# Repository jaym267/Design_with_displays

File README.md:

# Design with Displays – Week 4: RGB Mood Light

For week 4 of Hack Club Half-Life, I designed a small RGB mood light board. A Seeed XIAO RP2040 drives a 5 mm RGB LED. A push button cycles through 7 colours, and a slide potentiometer sets the brightness from off to full.

## What I did
 
### 1. Planned the project
I followed the Tier 1 "5 mm LEDs" guide and picked the RGB mood light as my build: one common-cathode RGB LED, a slide pot, and a button, all controlled by a XIAO RP2040.

### 2. Drew the schematic in KiCad
- I created a new KiCad project and placed the XIAO RP2040, an RGB LED (LED_RKGB), three resistors, a 10 kΩ slide pot, a push button, and the power symbols.
- I picked the resistor values from the LED's forward voltage: 270 Ω for red (about 2.0 V) and 100 Ω for green and blue (about 3.0 V), all running from a 3.3 V pin.
- I wired each colour through its resistor to the LED, the LED's common cathode to GND, the pot between 3V3 and GND, and the button to GND.
- I used net labels to connect the parts to the XIAO pins: LED_RED → D6, LED_GREEN → D7, LED_BLUE → D8, SLIDER → D0/A0, BUTTON → D1.

### 3. Passed the Electrical Rules Check
- I added PWR_FLAGs on the GND and +3V3 nets so KiCad knew where power comes from.
- I put no-connect flags on all 13 unused XIAO pins.
- The ERC finished with 0 errors.

### 4. Assigned footprints
- I used through-hole parts so they're easy to hand-solder: a 5 mm 4-pin RGB LED, axial resistors, a Bourns PTA4543 slide pot, and a 6 mm tactile switch.
- I fixed a missing-footprint problem by adding Seeed's OPL XIAO footprint library to my global KiCad libraries.

### 5. Laid out the PCB
- I made a 66 × 35.5 mm two-layer board.
- I placed the XIAO with its USB-C port at the top edge, the button beside it, the resistors lined up with the LED legs, and the slide pot along the bottom edge.
- I arranged the parts so none of the signal traces cross.

### 6. Routed the board
- I used 0.25 mm traces for the signals and a 0.5 mm trace for 3.3 V power.
- I filled the whole back layer with GND copper and connected the XIAO's GND pad to it with a via.

### 7. Passed the Design Rules Check
- I fixed four annular-ring errors on the LED by shrinking its holes from 0.9 mm to 0.8 mm.
- I fixed one unconnected-item error by adding a trace between the button's two "pad 1" legs.
- The DRC finished with 0 errors.

### 8. Wrote the firmware
- I wrote an Arduino sketch for the Seeed XIAO RP2040 using the arduino-pico core.
- Each button press steps through 7 colours, and the slider sets brightness with PWM.
- It compiles successfully, and I'll flash it at build week.
-

### 9. Pushed everything to GitHub
This repo holds the KiCad project (`rgb-light/`) and the firmware (`rgb_light_firmware/`).

## Bill of Materials

| Qty | Part | Part Number | Where to buy | Approx. price |
|---|---|---|---|---|
| 1 | Seeed Studio XIAO RP2040 | 102010428 | [DigiKey](https://www.digikey.com/en/products/detail/seeed-technology-co-ltd/102010428/14672129) | $4.68 |
| 1 | 5 mm RGB LED, diffused, common cathode | SparkFun COM-09264 | [DigiKey](https://www.digikey.com/en/products/detail/sparkfun-electronics/09264/9770728) | $2.30 |
| 2 | 100 Ω resistor, 1/4 W, through-hole | Stackpole CF14JT100R | [DigiKey](https://www.digikey.com/en/products/detail/stackpole-electronics-inc/CF14JT100R/1830327) | $0.20 |
| 1 | 270 Ω resistor, 1/4 W, through-hole | Stackpole CF14JT270R | [DigiKey](https://www.digikey.com/en/products/result?keywords=CF14JT270R) | $0.10 |
| 1 | Slide potentiometer, 10 kΩ linear, 45 mm | Bourns PTA4543-2015DPB103 | [DigiKey](https://www.digikey.com/en/products/detail/bourns-inc/PTA4543-2015DPB103/3534245) | $1.76 |
| 1 | 6 × 6 mm tactile push button, through-hole | Omron B3F-1000 | [DigiKey](https://www.digikey.com/en/products/detail/omron-electronics-inc-emc-div/B3F-1000/33150) | $0.27 |
| 5 | Custom 2-layer PCB, 66 × 35.5 mm | rgb-light gerbers | [JLCPCB](https://jlcpcb.com) | $2.00 |
| | | | **Total (before shipping)** | **≈ $11.31** |

## Tools
- KiCad 10 for the schematic and PCB
- Arduino IDE with the arduino-pico core for the firmware
- I used Claude (AI) as a step-by-step guide. It also generated the net labels, part placement, and trace routing in the KiCad files, and I reviewed and verified them with ERC and DRC.

## Time spent

8 hours

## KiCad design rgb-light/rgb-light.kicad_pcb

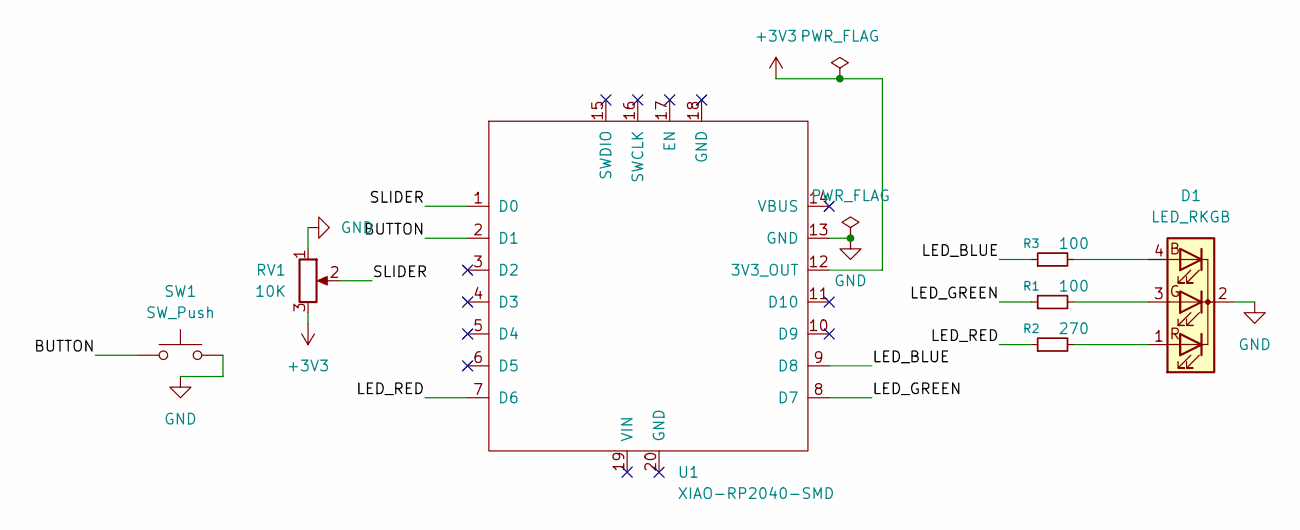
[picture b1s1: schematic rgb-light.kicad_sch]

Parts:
D1: LED_RKGB; LED_D5.0mm-4_RGB
R1, R3: 100; R_Axial_DIN0207_L6.3mm_D2.5mm_P7.62mm_Horizontal
R2: 270; R_Axial_DIN0207_L6.3mm_D2.5mm_P7.62mm_Horizontal
RV1: 10K; Potentiometer_Bourns_PTA4543_Single_Slide
SW1: SW_Push; SW_PUSH_6mm
U1: XIAO-RP2040-SMD

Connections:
+3V3: RV1.3, U1.12 (3V3_OUT)
/BUTTON: SW1.1, U1.2 (D1)
/LED_BLUE: R3.1, U1.9 (D8)
/LED_GREEN: R1.1, U1.8 (D7)
/LED_RED: R2.1, U1.7 (D6)
/SLIDER: RV1.2, U1.1 (D0)
GND: D1.2 (K), RV1.1, SW1.2, U1.13 (GND)
unnamed: D1.4 (BA), R3.2
unnamed: D1.3 (GA), R1.2
unnamed: D1.1 (RA), R2.2

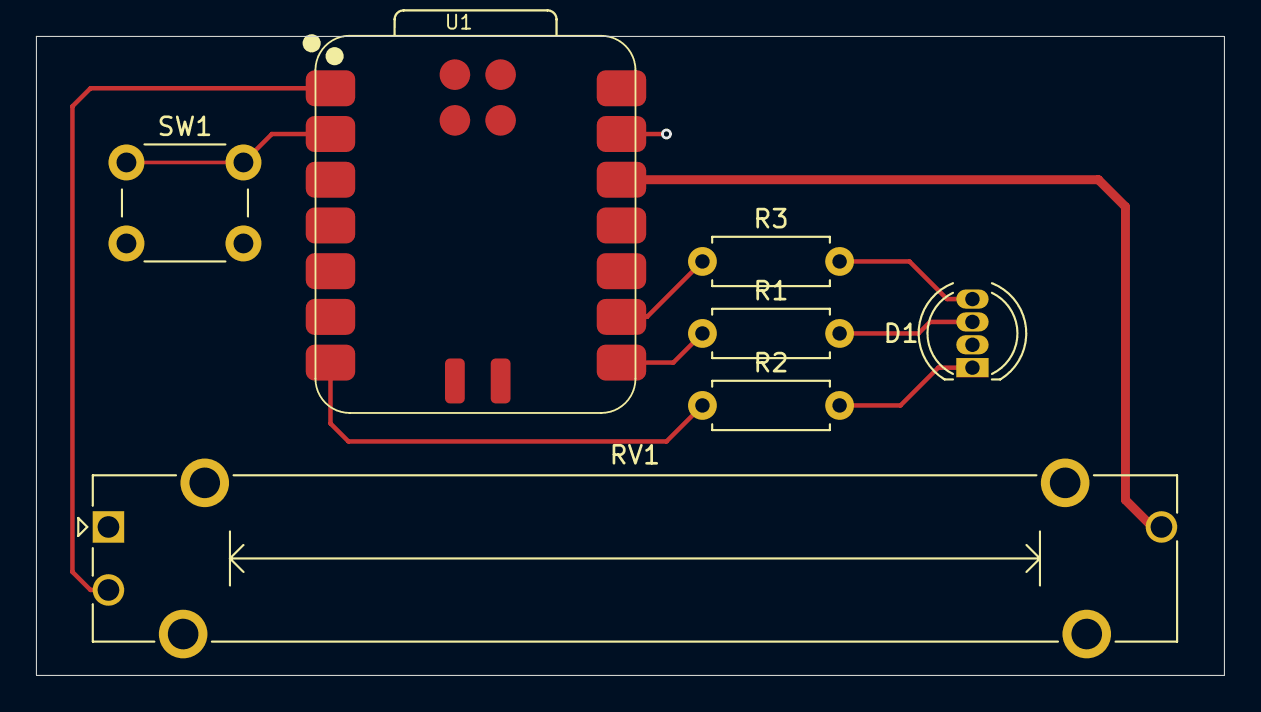
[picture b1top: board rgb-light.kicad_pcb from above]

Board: 2 copper layers, 66.0 x 35.5 mm, 7 parts (0 on the bottom side), 10 nets.
